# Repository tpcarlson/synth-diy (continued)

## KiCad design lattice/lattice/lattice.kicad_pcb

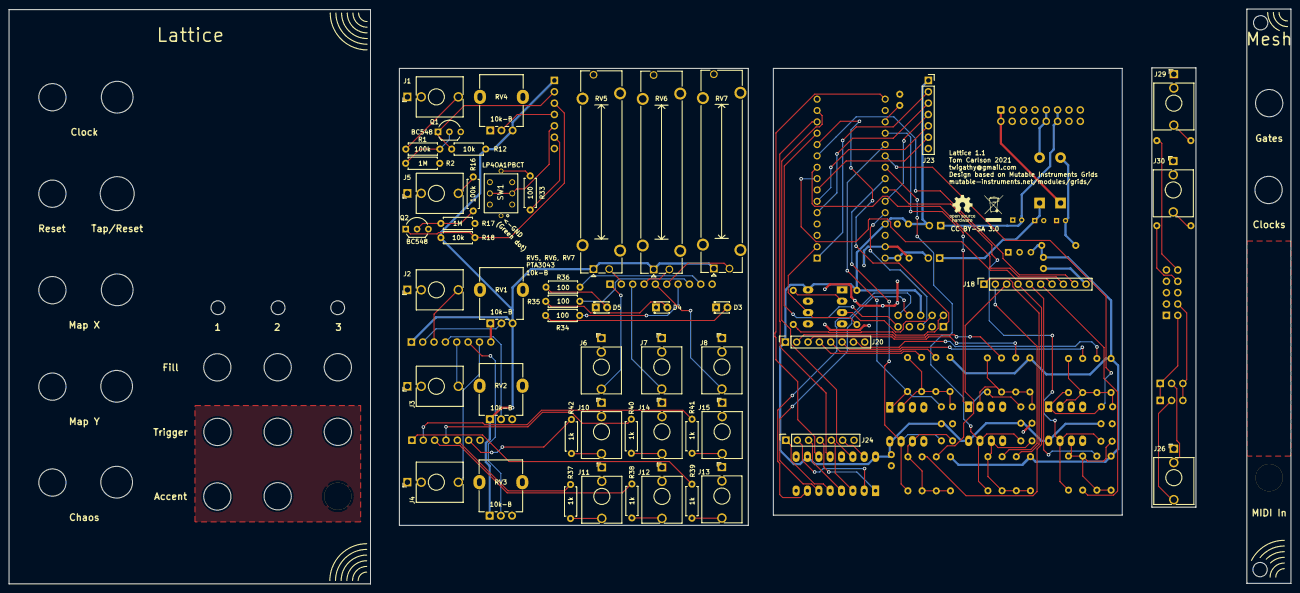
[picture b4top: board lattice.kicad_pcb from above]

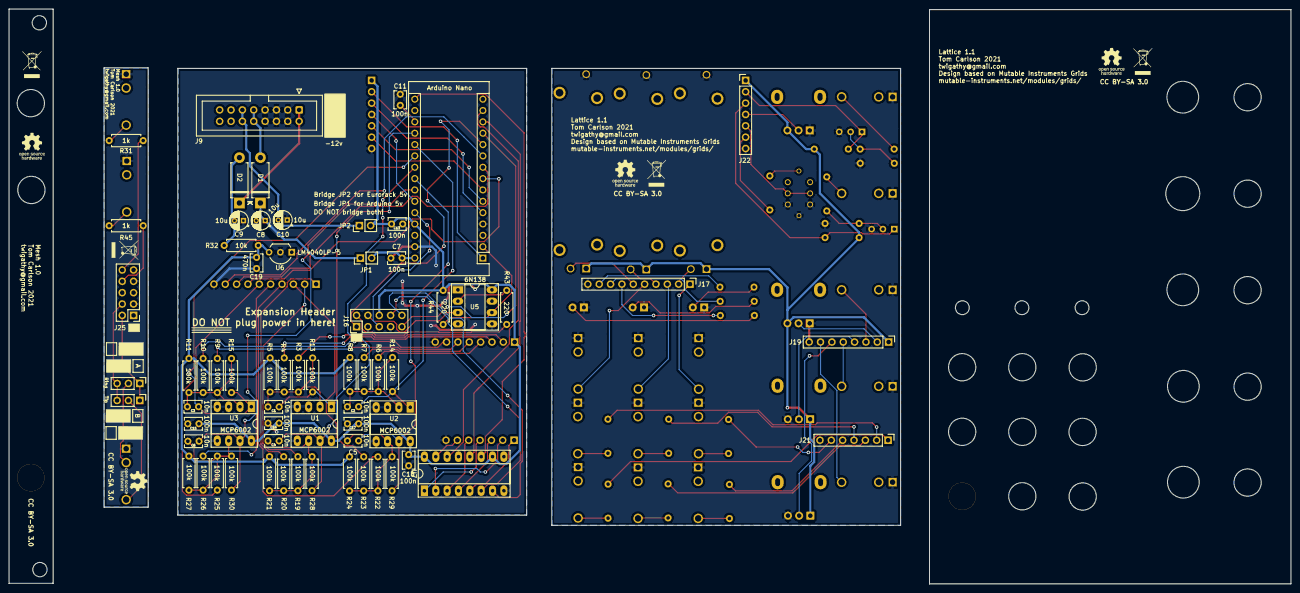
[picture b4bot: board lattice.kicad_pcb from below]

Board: 2 copper layers, 286.9 x 128.7 mm, 127 parts (74 on the bottom side), 78 nets.

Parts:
A1: Arduino_Nano_v3.x; Arduino_Nano
C1, C2, C3, C4, C5, C6: 10n; C_Disc_D3.8mm_W2.6mm_P2.50mm
C7, C11, C13, C15, C16, C17, C18: 100n; C_Disc_D3.8mm_W2.6mm_P2.50mm
C8, C9, C10: 10u; CP_Radial_D4.0mm_P2.00mm
C19: 470n; C_Disc_D3.8mm_W2.6mm_P2.50mm
D1, D2: D_Schottky; D_DO-15_P10.16mm_Horizontal
D3, D4, D5: LED; LED_D1.8mm_W3.3mm_H2.4mm
J1, J2, J3, J4, J5, J6, J7, J8, J10, J11, J12, J13, J14, J15, J29, J30: AudioJack2; Jack_3.5mm_QingPu_WQP-PJ398SM_Vertical_CircularHoles
J9: Conn_02x08_Odd_Even; IDC-Header_2x08_P2.54mm_Vertical
J16, J25: Conn_02x05_Odd_Even; PinHeader_2x05_P2.54mm_Vertical
J17: Conn_01x10; PinHeader_1x10_P2.54mm_Vertical
J18: Conn_01x10; PinSocket_1x10_P2.54mm_Vertical
J19: Conn_01x08; PinHeader_1x08_P2.54mm_Vertical
J20: Conn_01x08; PinSocket_1x08_P2.54mm_Vertical
J21, J22: Conn_01x07; PinHeader_1x07_P2.54mm_Vertical
J23, J24: Conn_01x07; PinSocket_1x07_P2.54mm_Vertical
J26, J26#2, J26#4, J26#5, J26#6: WEEE; WEEE-Logo_4.2x6mm_SilkScreen
J26#3: AudioJack3; Jack_3.5mm_QingPu_WQP-PJ398SM_Vertical_CircularHoles
J27, J27#2, J27#4, J27#5, J27#6: OSHW; OSHW-Logo_5.7x6mm_SilkScreen
J27#3, J28: Conn_01x03; PinHeader_1x03_P2.54mm_Vertical
JP1, JP2: Jumper; PinHeader_1x02_P2.54mm_Vertical
Q1, Q2: BC548; TO-92_Inline_Wide
R1, R3, R4, R5, R6, R7, R8, R9, R10, R11, R13, R14, R15, R16, R19, R20, R21, R22, R23, R24, R25, R26, R27, R28, R29, R30: 100k; R_Axial_DIN0207_L6.3mm_D2.5mm_P7.62mm_Horizontal
R2, R17: 1M; R_Axial_DIN0207_L6.3mm_D2.5mm_P7.62mm_Horizontal
R12, R18, R32: 10k; R_Axial_DIN0207_L6.3mm_D2.5mm_P7.62mm_Horizontal
R31, R37, R38, R39, R40, R41, R42, R45: 1k; R_Axial_DIN0207_L6.3mm_D2.5mm_P7.62mm_Horizontal
R33, R34, R35, R36: 100; R_Axial_DIN0207_L6.3mm_D2.5mm_P7.62mm_Horizontal
R43, R44: 220; R_Axial_DIN0207_L6.3mm_D2.5mm_P7.62mm_Horizontal
RV1, RV2, RV3, RV4: 10k-B; Potentiometer_Alpha_RD901F-40-00D_Single_Vertical
RV5, RV6, RV7: 10k-B; Potentiometer_Bourns_PTA3043_Single_Slide
SW1: LP4OA1PBCT
U1, U2, U3: MCP6002-xP; DIP-8_W7.62mm_Socket_LongPads
U5: 6N138; DIP-8_W7.62mm_Socket_LongPads
U6: LM4040LP-5; TO-92_Inline_Wide
U7: 74HC595; DIP-16_W7.62mm_Socket_LongPads
U$1: EURORACK_TEMPLATE

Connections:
+5V: A1.27, C13.1, C15.1, C16.1, C17.1, C18.2, J16.6, J19.1, J20.1, J22.1, J23.1, JP2.2, R12.1, R18.1, R44.1, RV1.3, RV2.1, RV3.1, RV4.3, RV5.1, RV6.1, RV7.1, U1.8, U2.8, U3.8, U5.8, U7.10, U7.16
+12V: C8.1, D1.1, JP1.1
-12V: C9.2, D2.2, R32.1
/5V_POWER_CONNECTOR: C10.2, J9.11, J9.12, JP2.1
/ARDUINO_POWER_12v: A1.30, C7.2, JP1.2
/CH1A: J21.6, J24.6, R42.2, U7.15
/CH1B: J21.5, J24.5, R37.2, U7.3
/CH1_CV: A1.22, C4.1, R28.1, U1.7
/CH1_JACK: J6.T, J17.1, J18.1, R20.2
/CH1_POT: J17.2, J18.2, R19.2, RV5.2
/CH2A: J21.4, J24.4, R40.2, U7.1
/CH2B: J21.3, J24.3, R38.2, U7.4
/CH2_CV: A1.23, C5.1, R29.1, U2.7
/CH2_JACK: J7.T, J17.3, J18.3, R23.2
/CH2_POT: J17.4, J18.4, R22.2, RV6.2
/CH3A: J21.2, J24.2, R41.2, U7.2
/CH3B: J21.1, J24.1, R39.2, U7.5
/CH3_CV: A1.24, C6.1, R30.1, U3.7
/CH3_JACK: J8.T, J17.5, J18.5, R26.2
/CH3_POT: J17.6, J18.6, R25.2, RV7.2
/EXPANSION_1: A1.11, J16.1
/EXPANSION_2: A1.12, J16.9
/EXPANSION_3: A1.26, J16.5
/EXT_MIDI_IN_PIN_4: J16.2, J25.2, J27#3.1, J28.1, R43.2
/EXT_MIDI_IN_PIN_5: J16.4, J25.4, J27#3.3, J28.3, U5.3
/EXT_RANDOM_CLOCK: J16.8, J25.8, R45.1, U7.6
/EXT_RANDOM_GATE: J16.10, J25.10, R31.1, U7.7
/IN_CLOCK: A1.1, J22.2, J23.2, Q1.1, R12.2
/IN_MIDI: A1.2, R44.2, U5.6
/IN_RESET: A1.5, J22.3, J23.3, Q2.1, R18.2
/LED_CH1: A1.10, J17.9, J18.9, R36.2
/LED_CH2: A1.9, J17.8, J18.8, R35.2
/LED_CH3: A1.8, J17.7, J18.7, R34.2
/LED_CLOCK: A1.7, J22.6, J23.6, R33.2
/MIDI_RING: J26#3.R, J27#3.2
/MIDI_TIP: J26#3.T, J28.2
/MOSI: A1.14, U7.14
/RAND_JACK: J4.T, J19.7, J20.7, R10.2
/RAND_POT: J19.6, J20.6, R9.2, RV3.2
/REF_-5: C19.1, R5.2, R8.2, R11.2, R21.2, R24.2, R27.2, R32.2, U6.3
/RND_CV: A1.21, C3.1, R15.1, U3.1
/SCK: A1.16, U7.11
/SS: A1.13, U7.12
/SW_RESET: A1.6, J22.5, J23.5, SW1.P2, SW1.P5
/TEMPO: A1.25, J22.4, J23.4, RV4.2
/X_CV: A1.19, C1.1, R13.1, U1.1
/X_JACK: J2.T, J19.3, J20.3, R4.2
/X_POT: J19.2, J20.2, R3.2, RV1.2
/Y_CV: A1.20, C2.1, R14.1, U2.1
/Y_JACK: J3.T, J19.5, J20.5, R7.2
/Y_POT: J19.4, J20.4, R6.2, RV2.2
Earth: A1.4, A1.29, C7.1, C8.2, C9.1, C10.1, C11.2, C13.2, C15.2, C16.2, C17.2, C18.1, C19.2, D3.1, D4.1, D5.1, J1.S, J2.S, J3.S, J4.S, J5.S, J6.S, J7.S, J8.S, J9.3, J9.4, J9.5, J9.6, J9.7, J9.8, J10.S, J11.S, J12.S, J13.S, J14.S, J15.S, J16.3, J16.7, J17.10, J18.10, J19.8, J20.8, J21.7, J22.7, J23.7, J24.7, J25.3, J25.7, J26#3.S, J29.S, J30.S, Q1.3, Q2.3, R2.2, R17.2, RV1.1, RV2.3, RV3.3, RV4.1, RV5.3, RV6.3, RV7.3, SW1.L2, SW1.P3, SW1.P6, U1.3, U1.4, U1.5, U2.3, U2.4, U2.5, U3.3, U3.4, U3.5, U5.5, U6.2, U7.8, U7.13
unnamed: A1.18, C11.1
unnamed: C1.2, R3.1, R4.1, R5.1, R13.2, U1.2
unnamed: C2.2, R6.1, R7.1, R8.1, R14.2, U2.2
unnamed: C3.2, R9.1, R10.1, R11.1, R15.2, U3.2
unnamed: C4.2, R19.1, R20.1, R21.1, R28.2, U1.6
unnamed: C5.2, R22.1, R23.1, R24.1, R29.2, U2.6
unnamed: C6.2, R25.1, R26.1, R27.1, R30.2, U3.6
unnamed: D1.2, J9.9, J9.10
unnamed: D2.1, J9.1, J9.2
unnamed: D3.2, R34.1
unnamed: D4.2, R35.1
unnamed: D5.2, R36.1
unnamed: J1.T, R1.2
unnamed: J5.T, R16.2
unnamed: J10.T, R42.1
unnamed: J11.T, R37.1
unnamed: J12.T, R38.1
unnamed: J13.T, R39.1
unnamed: J14.T, R40.1
unnamed: J15.T, R41.1
unnamed: J29.T, R31.2
unnamed: J30.T, R45.2
unnamed: Q1.2, R1.1, R2.1
unnamed: Q2.2, R16.1, R17.1
unnamed: R33.1, SW1.L1
unnamed: R43.1, U5.2

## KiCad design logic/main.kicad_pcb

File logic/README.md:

# Logic

##### What is this?

A 4-channel logic module using CD4xxx chips

##### How much power does it use?

As measured by the Joranalogue Test 3, around 50 mA on +12v and 15 mA on -12v at peak. The 5v rail is unused.

##### Where does the design come from?

Originally, this is from the Modular in a Week series on YouTube (www.youtube.com/watch?v=Bv7GWUPW-EA) by Kristian Blåsol. I tweaked the design a little and added some features such as the strip of LEDs at the top of the module, and made the swappable logic IC on a daughterboard rather than in an IC socket.

##### Are there any rare/weird parts used?

You will need to get hold of the proper kind of logic chip for the logic operation you want to support. In the one I have built, I used a CD4070 quad xor.

The design is also partially SMT for the resistors, diodes and TL074 ICs, but otherwise uses common through-hole parts.

##### Are there any problems with the design?

Nope!

##### Do you have a BOM/Mouser cart/Tayda links?

Sorry, no. Things go out of stock so frequently it'd be a lot of work to keep these up to date. Everything in this project is easy to source though, so you should not have any trouble.

##### Can I buy PCBs or a kit?

Available as a [DIY Kit](https://www.tindie.com/products/divergentwaves/logic/) from Tindie

##### Other resources

- [BOM](BOM.md)
- [Assembly guide](ASSEMBLY.md)

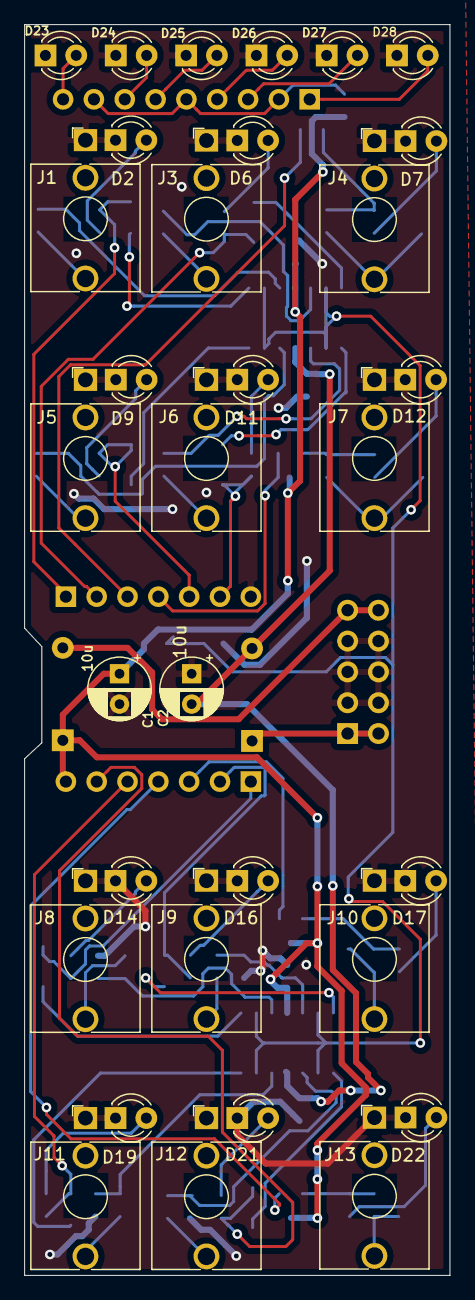
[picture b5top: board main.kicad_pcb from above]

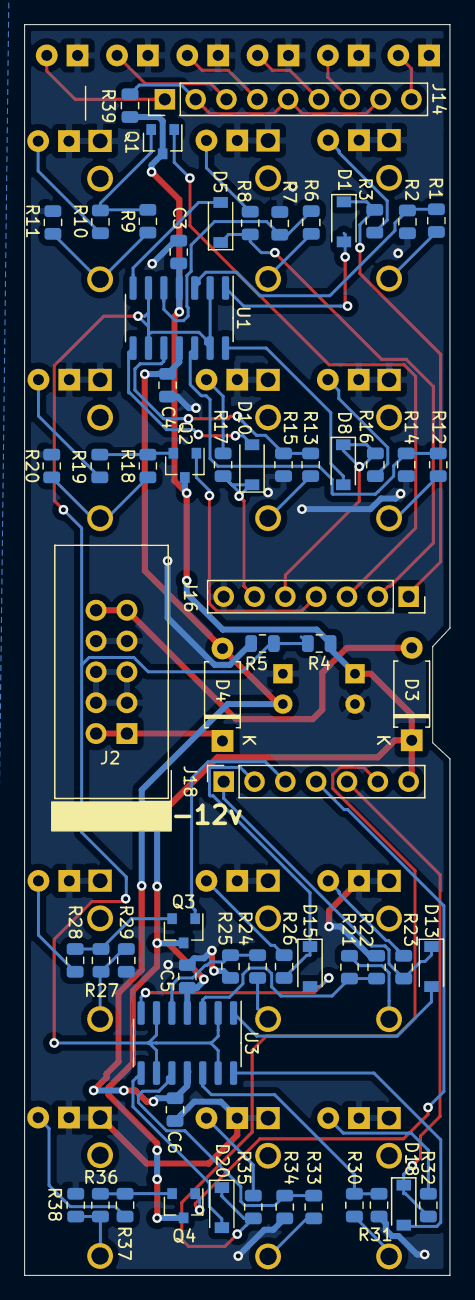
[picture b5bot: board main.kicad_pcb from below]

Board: 2 copper layers, 35.1 x 103.1 mm, 95 parts (63 on the bottom side), 69 nets.

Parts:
C1, C2: 10u; CP_Radial_D5.0mm_P2.50mm
C3, C4, C5, C6: 100n; C_0805_2012Metric
D1, D5, D8, D10, D13, D15, D18, D20: 1N4148W; D_SOD-123
D2, D6, D7, D9, D11, D12, D14, D16, D17, D19, D21, D22, D23, D24, D25, D26, D27, D28: LED; LED_D3.0mm
D3, D4: D_Schottky; D_A-405_P7.62mm_Horizontal
J1, J3, J4, J5, J6, J7, J8, J9, J10, J11, J12, J13: AudioJack2; Jack_3.5mm_QingPu_WQP-PJ398SM_Vertical_CircularHoles
J2: Conn_02x05_Odd_Even; IDC-Header_2x05_P2.54mm_Vertical
J14: Conn_01x09; PinHeader_1x09_P2.54mm_Vertical
J16, J18: Conn_01x07; PinSocket_1x07_P2.54mm_Vertical
Q1, Q2, Q3, Q4: MMBT3904; SOT-23
R1, R6, R9, R11, R12, R13, R18, R20, R21, R24, R27, R29, R30, R33, R36, R38: 1k; R_0805_2012Metric
R2, R4, R7, R14, R15, R22, R25, R31, R34: 100k; R_0805_2012Metric
R3, R8, R10, R16, R17, R19, R23, R26, R28, R32, R35, R37, R39: 2k7; R_0805_2012Metric
R5: 10k; R_0805_2012Metric
U1, U3: TL074; SOIC-14_3.9x8.7mm_P1.27mm

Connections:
+12V: C1.1, C3.2, C5.2, D3.1, J18.7, Q1.3, Q2.3, Q3.3, Q4.3, R4.1, R39.1, U1.4, U3.4
-12V: C2.2, C4.1, C6.1, D4.2, U1.11, U3.11
Earth: C1.2, C2.1, C3.1, C4.2, C5.1, C6.2, D2.1, D6.1, D7.1, D9.1, D11.1, D12.1, D14.1, D16.1, D17.1, D19.1, D21.1, D22.1, D23.1, D24.1, D25.1, D26.1, D27.1, D28.1, J1.S, J2.3, J2.4, J2.5, J2.6, J2.7, J2.8, J3.S, J4.S, J5.S, J6.S, J7.S, J8.S, J9.S, J10.S, J11.S, J12.S, J13.S, J16.7, R2.2, R5.2, R7.2, R11.1, R14.2, R15.2, R20.1, R22.2, R25.2, R29.1, R31.2, R34.2, R38.1
unnamed: D1.1, J16.1, R3.1
unnamed: D1.2, U1.1
unnamed: D2.2, R3.2
unnamed: D3.2, J2.9, J2.10
unnamed: D4.1, J2.1, J2.2
unnamed: D5.1, J16.2, R8.1
unnamed: D5.2, U1.7
unnamed: D6.2, R8.2
unnamed: D7.2, R10.1
unnamed: D8.1, J16.5, R16.1
unnamed: D8.2, U1.14
unnamed: D9.2, R16.2
unnamed: D10.1, J16.6, R17.1
unnamed: D10.2, U1.8
unnamed: D11.2, R17.2
unnamed: D12.2, R19.1
unnamed: D13.1, J18.1, R23.1
unnamed: D13.2, U3.1
unnamed: D14.2, R23.2
unnamed: D15.1, J18.2, R26.1
unnamed: D15.2, U3.7
unnamed: D16.2, R26.2
unnamed: D17.2, R28.1
unnamed: D18.1, J18.5, R32.1
unnamed: D18.2, U3.14
unnamed: D19.2, R32.2
unnamed: D20.1, J18.6, R35.1
unnamed: D20.2, U3.8
unnamed: D21.2, R35.2
unnamed: D22.2, R37.1
unnamed: D23.2, J14.9
unnamed: D24.2, J14.7
unnamed: D25.2, J14.6
unnamed: D26.2, J14.4
unnamed: D27.2, J14.3
unnamed: D28.2, J14.1
unnamed: J1.T, R1.2
unnamed: J3.T, R6.2
unnamed: J4.T, R9.1, R11.2
unnamed: J5.T, R12.2
unnamed: J6.T, R13.2
unnamed: J7.T, R18.1, R20.2
unnamed: J8.T, R21.2
unnamed: J9.T, R24.2
unnamed: J10.T, R27.1, R29.2
unnamed: J11.T, R30.2
unnamed: J12.T, R33.2
unnamed: J13.T, R36.1, R38.2
unnamed: J14.2, J14.5, J14.8, R39.2
unnamed: J16.3, Q1.1
unnamed: J16.4, Q2.1
unnamed: J18.3, Q3.1
unnamed: J18.4, Q4.1
unnamed: Q1.2, R9.2, R10.2
unnamed: Q2.2, R18.2, R19.2
unnamed: Q3.2, R27.2, R28.2
unnamed: Q4.2, R36.2, R37.2
unnamed: R1.1, R2.1, U1.3
unnamed: R6.1, R7.1, U1.5
unnamed: R12.1, R14.1, U1.12
unnamed: R13.1, R15.1, U1.10
unnamed: R21.1, R22.1, U3.3
unnamed: R24.1, R25.1, U3.5
unnamed: R30.1, R31.1, U3.12
unnamed: R33.1, R34.1, U3.10
V_COMPARISON: R4.2, R5.1, U1.2, U1.6, U1.9, U1.13, U3.2, U3.6, U3.9, U3.13

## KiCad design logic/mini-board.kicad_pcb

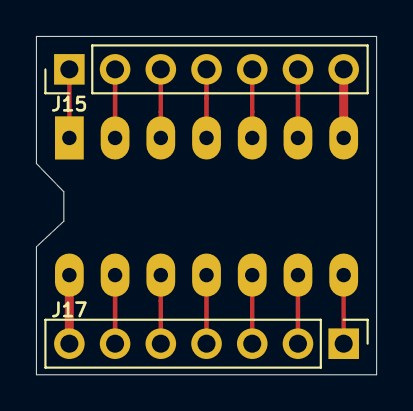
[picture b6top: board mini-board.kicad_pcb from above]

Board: 2 copper layers, 18.9 x 18.8 mm, 3 parts (1 on the bottom side), 14 nets.

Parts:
J15, J17: Conn_01x07; PinHeader_1x07_P2.54mm_Vertical
U2: 4070; DIP-14_W7.62mm_Socket_LongPads

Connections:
+12V: J17.7, U2.14
Earth: J15.7, U2.7
unnamed: J15.1, U2.1
unnamed: J15.2, U2.2
unnamed: J15.5, U2.5
unnamed: J15.6, U2.6
unnamed: J17.1, U2.8
unnamed: J17.2, U2.9
unnamed: J17.5, U2.12
unnamed: J17.6, U2.13
unnamed: J15.3, U2.3
unnamed: J15.4, U2.4
unnamed: J17.3, U2.10
unnamed: J17.4, U2.11
